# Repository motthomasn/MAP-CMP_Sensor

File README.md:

# MAP-CMP_Sensor
Small module combining a MAP sensor and engine phase sensor (camshaft posn) for internal combustion engine management

This module was built for my CBR250RRi project. The aim was to allow an aftermarket ECU to achieve 720deg synchronisation or engine phase detection without the use of a physical camshaft position sensor being installed on the engine. It has been designed for use on a port throttled engine and sample the pressure pulses from a single inlet port. 

The board uses an NXP pressure sensor to measure the pressure pulses. The pressure signal is passed to an LM397 comparator and compared to a reference voltage which can be adjusted via trim pot. The output signal from the comparator is normally high but when the pressure signal falls below the reference voltage, the output is pulled low. With the reference voltage set correctly, a reliable "cam position" signal can be achieved consisting of a single pulse per engine cycle.

Note: In a port throttled engine, the pressure signal may not be strong enough to produce a reliable signal throughout the engine speed/load range. In my application this is fine as the ECU I am working with (Life Racing F88R) allows the option to ignore the engine phase signal once 720deg synchronisation has been achieved. This means that the signal only has to be reliable during starting and idle.

For further details on the CBR250RRi project, refer to the website https://www.cbr250rri.com/.

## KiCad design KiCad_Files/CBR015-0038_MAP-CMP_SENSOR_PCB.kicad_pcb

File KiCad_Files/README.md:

This folder contains the KiCad files for the MAP-CMP module.

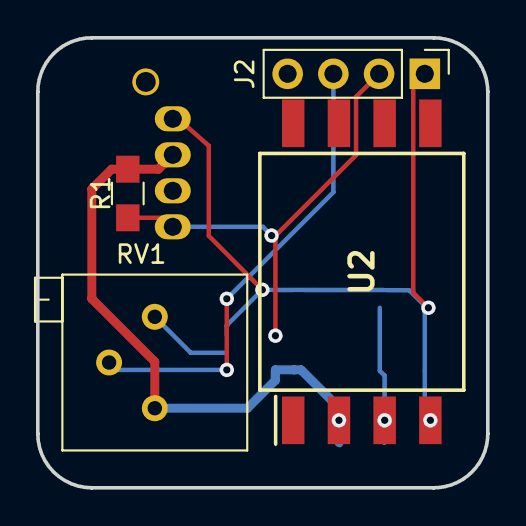
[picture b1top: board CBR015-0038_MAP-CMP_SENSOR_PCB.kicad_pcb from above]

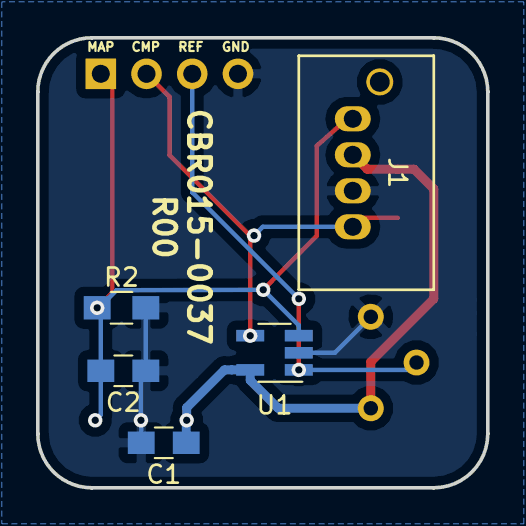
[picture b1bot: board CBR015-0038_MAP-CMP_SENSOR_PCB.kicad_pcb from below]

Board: 2 copper layers, 25.0 x 25.0 mm, 9 parts (5 on the bottom side), 5 nets.

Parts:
C1: 100nF; C_0805_HandSoldering
C2: 47pF; C_0805_HandSoldering
J1: B04B-JWPF-SK-R; JST_B04B-JWPF-SK-R
J2: DEBUG_CONN; Pin_Header_Straight_1x04_Pitch2.54mm
R1: 10K; R_0805_HandSoldering
R2: 51K; R_0805_HandSoldering
RV1: R_POT; Potentiometer_Bourns_3296P_Horizontal
U1: LM397; SOT-23-5_HandSoldering
U2: MPXA6115A; 98ASB17757C

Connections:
+5V: C1.1, J1.3, R1.1, RV1.3, U1.5, U2.2
CMP_SIG: J1.1, J2.2, R1.2, U1.4
Earth: C1.2, C2.1, J1.2, J2.4, R2.2, RV1.1, U1.2, U2.3
MAP_SIG: C2.2, J1.4, J2.1, R2.1, U1.3, U2.4
VREF: J2.3, RV1.2, U1.1
